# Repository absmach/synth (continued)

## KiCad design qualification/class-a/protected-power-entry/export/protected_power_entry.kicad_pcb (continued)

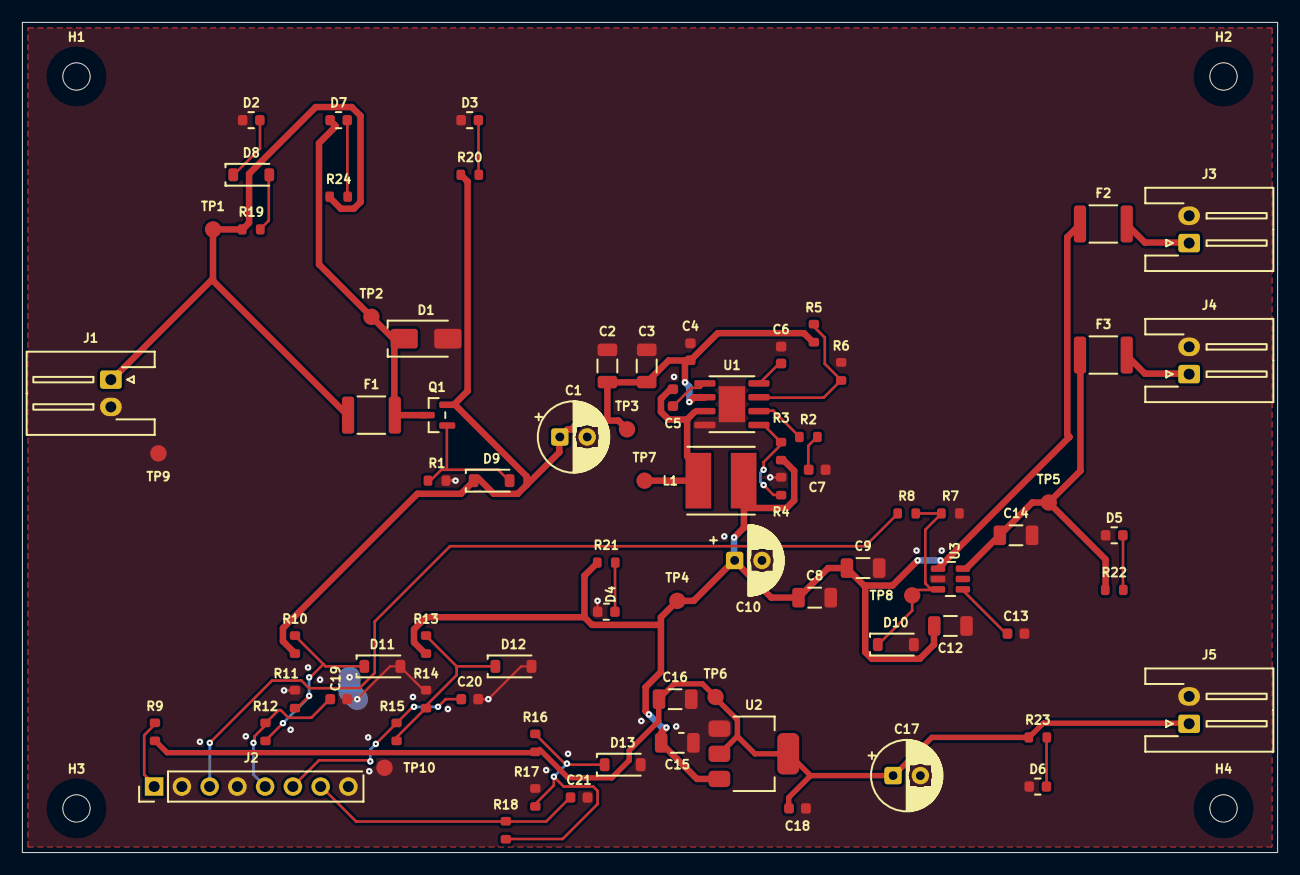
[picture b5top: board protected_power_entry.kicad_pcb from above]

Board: 2 copper layers, 114.9 x 76.0 mm, 84 parts (0 on the bottom side), 34 nets.

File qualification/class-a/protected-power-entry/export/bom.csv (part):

refdes,value,kind,description,kicad_symbol,kicad_footprint,lcsc_pn,mpn
C1,100uF 25V,capacitor,"100µF 25V aluminium electrolytic, radial through-hole, polarised",Device:C_Polarized,Capacitor_THT:CP_Radial_D6.3mm_P2.50mm,,
C10,100uF 25V,capacitor,"100µF 25V aluminium electrolytic, radial through-hole, polarised",Device:C_Polarized,Capacitor_THT:CP_Radial_D6.3mm_P2.50mm,,
C12,10uF 10V,capacitor,"Generic 1206 ceramic capacitor, any value",Device:C,Capacitor_SMD:C_1206_3216Metric,,
C13,2.2nF,capacitor,"Generic 0603 MLCC, X7R/X5R, any value",Device:C,Capacitor_SMD:C_0603_1608Metric,,
C14,22uF 10V,capacitor,"Generic 1206 ceramic capacitor, any value",Device:C,Capacitor_SMD:C_1206_3216Metric,,
C15,10uF 10V,capacitor,"Generic 1206 ceramic capacitor, any value",Device:C,Capacitor_SMD:C_1206_3216Metric,,
C16,10uF 10V,capacitor,"Generic 1206 ceramic capacitor, any value",Device:C,Capacitor_SMD:C_1206_3216Metric,,
C17,100uF 25V,capacitor,"100µF 25V aluminium electrolytic, radial through-hole, polarised",Device:C_Polarized,Capacitor_THT:CP_Radial_D6.3mm_P2.50mm,,
C18,100nF,capacitor,"Generic 0603 MLCC, X7R/X5R, any value",Device:C,Capacitor_SMD:C_0603_1608Metric,,
C19,100nF,capacitor,"Generic 0603 MLCC, X7R/X5R, any value",Device:C,Capacitor_SMD:C_0603_1608Metric,,
C2,10uF 25V,capacitor,"Generic 1206 ceramic capacitor, any value",Device:C,Capacitor_SMD:C_1206_3216Metric,,
C20,100nF,capacitor,"Generic 0603 MLCC, X7R/X5R, any value",Device:C,Capacitor_SMD:C_0603_1608Metric,,
C21,100nF,capacitor,"Generic 0603 MLCC, X7R/X5R, any value",Device:C,Capacitor_SMD:C_0603_1608Metric,,
C3,10uF 25V,capacitor,"Generic 1206 ceramic capacitor, any value",Device:C,Capacitor_SMD:C_1206_3216Metric,,
C4,100nF,capacitor,"Generic 0603 MLCC, X7R/X5R, any value",Device:C,Capacitor_SMD:C_0603_1608Metric,,
C5,10nF,capacitor,"Generic 0603 MLCC, X7R/X5R, any value",Device:C,Capacitor_SMD:C_0603_1608Metric,,
C6,100nF,capacitor,"Generic 0603 MLCC, X7R/X5R, any value",Device:C,Capacitor_SMD:C_0603_1608Metric,,
C7,2.2nF,capacitor,"Generic 0603 MLCC, X7R/X5R, any value",Device:C,Capacitor_SMD:C_0603_1608Metric,,
C8,22uF 10V,capacitor,"Generic 1206 ceramic capacitor, any value",Device:C,Capacitor_SMD:C_1206_3216Metric,,
C9,22uF 10V,capacitor,"Generic 1206 ceramic capacitor, any value",Device:C,Capacitor_SMD:C_1206_3216Metric,,
D1,SMAJ13A,diode,"Littelfuse SMAJ13A 400 W unidirectional TVS, 13 V standoff, 14.4-15.9 V breakdown, 21.5 V max clamp at 18.6 A, DO-214AC (SMA)",Device:D_Zener,Diode_SMD:D_SMA,,SMAJ13A
D10,BZT52C5V1-TP,diode,"5.1V Zener diode, SOD-123",Device:D_Zener,Diode_SMD:D_SOD-123,C78728,BZT52C5V1-TP
D11,BZT52C3V3,diode,"BZT52C3V3 3.3 V +/-5 % 500 mW zener diode, SOD-123 (clamp for the ADC sample lines). No LCSC number asserted.",Device:D_Zener,Diode_SMD:D_SOD-123,,BZT52C3V3
D12,BZT52C3V3,diode,"BZT52C3V3 3.3 V +/-5 % 500 mW zener diode, SOD-123 (clamp for the ADC sample lines). No LCSC number asserted.",Device:D_Zener,Diode_SMD:D_SOD-123,,BZT52C3V3
D13,BZT52C3V3,diode,"BZT52C3V3 3.3 V +/-5 % 500 mW zener diode, SOD-123 (clamp for the ADC sample lines). No LCSC number asserted.",Device:D_Zener,Diode_SMD:D_SOD-123,,BZT52C3V3
D2,(no value),diode,"White surface-mount LED, 0603",Device:LED,LED_SMD:LED_0603_1608Metric,,
D3,(no value),diode,"Blue surface-mount LED, 0603",Device:LED,LED_SMD:LED_0603_1608Metric,,
D4,LTST-C190KGKT,diode,"Lite-On LTST-C190KGKT green AlInGaP LED, 0603, Vf 1.9 to 2.4V at 20mA",Device:LED,LED_SMD:LED_0603_1608Metric,,LTST-C190KGKT
D5,0603-GREEN,diode,"Green LED, 0603 package, ~2.2V Vf",Device:LED,LED_SMD:LED_0603_1608Metric,C72043,0603-GREEN
D6,(no value),diode,"Amber surface-mount LED, 0603",Device:LED,LED_SMD:LED_0603_1608Metric,,
D7,LTST-C190KRKT,diode,"Lite-On LTST-C190KRKT red AlInGaP LED, 0603, Vf 1.6 to 2.4V at 20mA",Device:LED,LED_SMD:LED_0603_1608Metric,,LTST-C190KRKT
D8,1N5819HW-7-F,diode,"Diodes Inc. 1N5819HW-7-F, 40 V 1 A Schottky diode, SOD-123, low forward voltage",Device:D_Schottky,Diode_SMD:D_SOD-123,C82544,1N5819HW-7-F
D9,BZT52C5V1-TP,diode,"5.1V Zener diode, SOD-123",Device:D_Zener,Diode_SMD:D_SOD-123,C78728,BZT52C5V1-TP
F1,1812L150/16DR,fuse,"Littelfuse 1812L150/16DR resettable fuse, 1.5 A hold, 16 V, 1812",Device:Polyfuse,Fuse:Fuse_1812_4532Metric,C207070,1812L150/16DR
F2,1812L150/16DR,fuse,"Littelfuse 1812L150/16DR resettable fuse, 1.5 A hold, 16 V, 1812",Device:Polyfuse,Fuse:Fuse_1812_4532Metric,C207070,1812L150/16DR
F3,1812L150/16DR,fuse,"Littelfuse 1812L150/16DR resettable fuse, 1.5 A hold, 16 V, 1812",Device:Polyfuse,Fuse:Fuse_1812_4532Metric,C207070,1812L150/16DR
H1,(no value),mounting_hole,M2.5 non-plated mounting hole (NPTH) for a board corner,Mechanical:MountingHole,MountingHole:MountingHole_2.5mm,,
H2,(no value),mounting_hole,M2.5 non-plated mounting hole (NPTH) for a board corner,Mechanical:MountingHole,MountingHole:MountingHole_2.5mm,,
H3,(no value),mounting_hole,M2.5 non-plated mounting hole (NPTH) for a board corner,Mechanical:MountingHole,MountingHole:MountingHole_2.5mm,,
H4,(no value),mounting_hole,M2.5 non-plated mounting hole (NPTH) for a board corner,Mechanical:MountingHole,MountingHole:MountingHole_2.5mm,,
J1,S2B-XH-A-1(LF)(SN),connector,"JST XH-series 2-pin wire-to-board connector, 2.0mm pitch",Connector_Generic:Conn_01x02,Connector_JST:JST_XH_S2B-XH-A-1_1x02_P2.50mm_Horizontal,C163035,S2B-XH-A-1(LF)(SN)
J2,(no value),connector,"1x8 through-hole pin header, 2.54 mm pitch, vertical (generic; no manufacturer part number or LCSC number asserted)",Connector_Generic:Conn_01x08,Connector_PinHeader_2.54mm:PinHeader_1x08_P2.54mm_Vertical,,
J3,S2B-XH-A-1(LF)(SN),connector,"JST XH-series 2-pin wire-to-board connector, 2.0mm pitch",Connector_Generic:Conn_01x02,Connector_JST:JST_XH_S2B-XH-A-1_1x02_P2.50mm_Horizontal,C163035,S2B-XH-A-1(LF)(SN)
J4,S2B-XH-A-1(LF)(SN),connector,"JST XH-series 2-pin wire-to-board connector, 2.0mm pitch",Connector_Generic:Conn_01x02,Connector_JST:JST_XH_S2B-XH-A-1_1x02_P2.50mm_Horizontal,C163035,S2B-XH-A-1(LF)(SN)
J5,S2B-XH-A-1(LF)(SN),connector,"JST XH-series 2-pin wire-to-board connector, 2.0mm pitch",Connector_Generic:Conn_01x02,Connector_JST:JST_XH_S2B-XH-A-1_1x02_P2.50mm_Horizontal,C163035,S2B-XH-A-1(LF)(SN)
L1,SRN6045TA-100M,inductor,"Bourns SRN6045TA-100M 10 uH semi-shielded power inductor, 6.0x6.0x4.2 mm. Datasheet at 25 C: DCR 52 mOhm +/-20 %, Irms 3.2 A (40 C rise), Isat 4.6 A (30 % inductance drop), SRF 25 MHz.",Device:L,Inductor_SMD:L_Bourns_SRN6045TA,,SRN6045TA-100M
Q1,AO3401A,transistor,"Alpha and Omega AO3401A P-channel MOSFET, 30 V, 4 A, SOT-23",Transistor_FET:Si2301CDS,Package_TO_SOT_SMD:SOT-23,,AO3401A
R1,47k,resistor,"Generic 0603 thick-film resistor, any value",Device:R_US,Resistor_SMD:R_0603_1608Metric,,
R10,10k,resistor,"Generic 0603 thick-film resistor, any value",Device:R_US,Resistor_SMD:R_0603_1608Metric,,
R11,2k,resistor,"Generic 0603 thick-film resistor, any value",Device:R_US,Resistor_SMD:R_0603_1608Metric,,
R12,1k,resistor,"Generic 0603 thick-film resistor, any value",Device:R_US,Resistor_SMD:R_0603_1608Metric,,
R13,10k,resistor,"Generic 0603 thick-film resistor, any value",Device:R_US,Resistor_SMD:R_0603_1608Metric,,
R14,10k,resistor,"Generic 0603 thick-film resistor, any value",Device:R_US,Resistor_SMD:R_0603_1608Metric,,
R15,1k,resistor,"Generic 0603 thick-film resistor, any value",Device:R_US,Resistor_SMD:R_0603_1608Metric,,
R16,10k,resistor,"Generic 0603 thick-film resistor, any value",Device:R_US,Resistor_SMD:R_0603_1608Metric,,
R17,10k,resistor,"Generic 0603 thick-film resistor, any value",Device:R_US,Resistor_SMD:R_0603_1608Metric,,
R18,1k,resistor,"Generic 0603 thick-film resistor, any value",Device:R_US,Resistor_SMD:R_0603_1608Metric,,
R19,3k,resistor,"Generic 0603 thick-film resistor, any value",Device:R_US,Resistor_SMD:R_0603_1608Metric,,
R2,10k,resistor,"Generic 0603 thick-film resistor, any value",Device:R_US,Resistor_SMD:R_0603_1608Metric,,
R20,3.3k,resistor,"Generic 0603 thick-film resistor, any value",Device:R_US,Resistor_SMD:R_0603_1608Metric,,
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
